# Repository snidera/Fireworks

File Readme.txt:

Fireworks controller.
Make things go boom from your phone...

Free to copy, use at your own risk.  This is somewhat hacked-together as I'm not a professional.    

BeagleboneBlack + i2c connected relay daughter boards 

Uses socket.io bonescript http-auth htpasswd

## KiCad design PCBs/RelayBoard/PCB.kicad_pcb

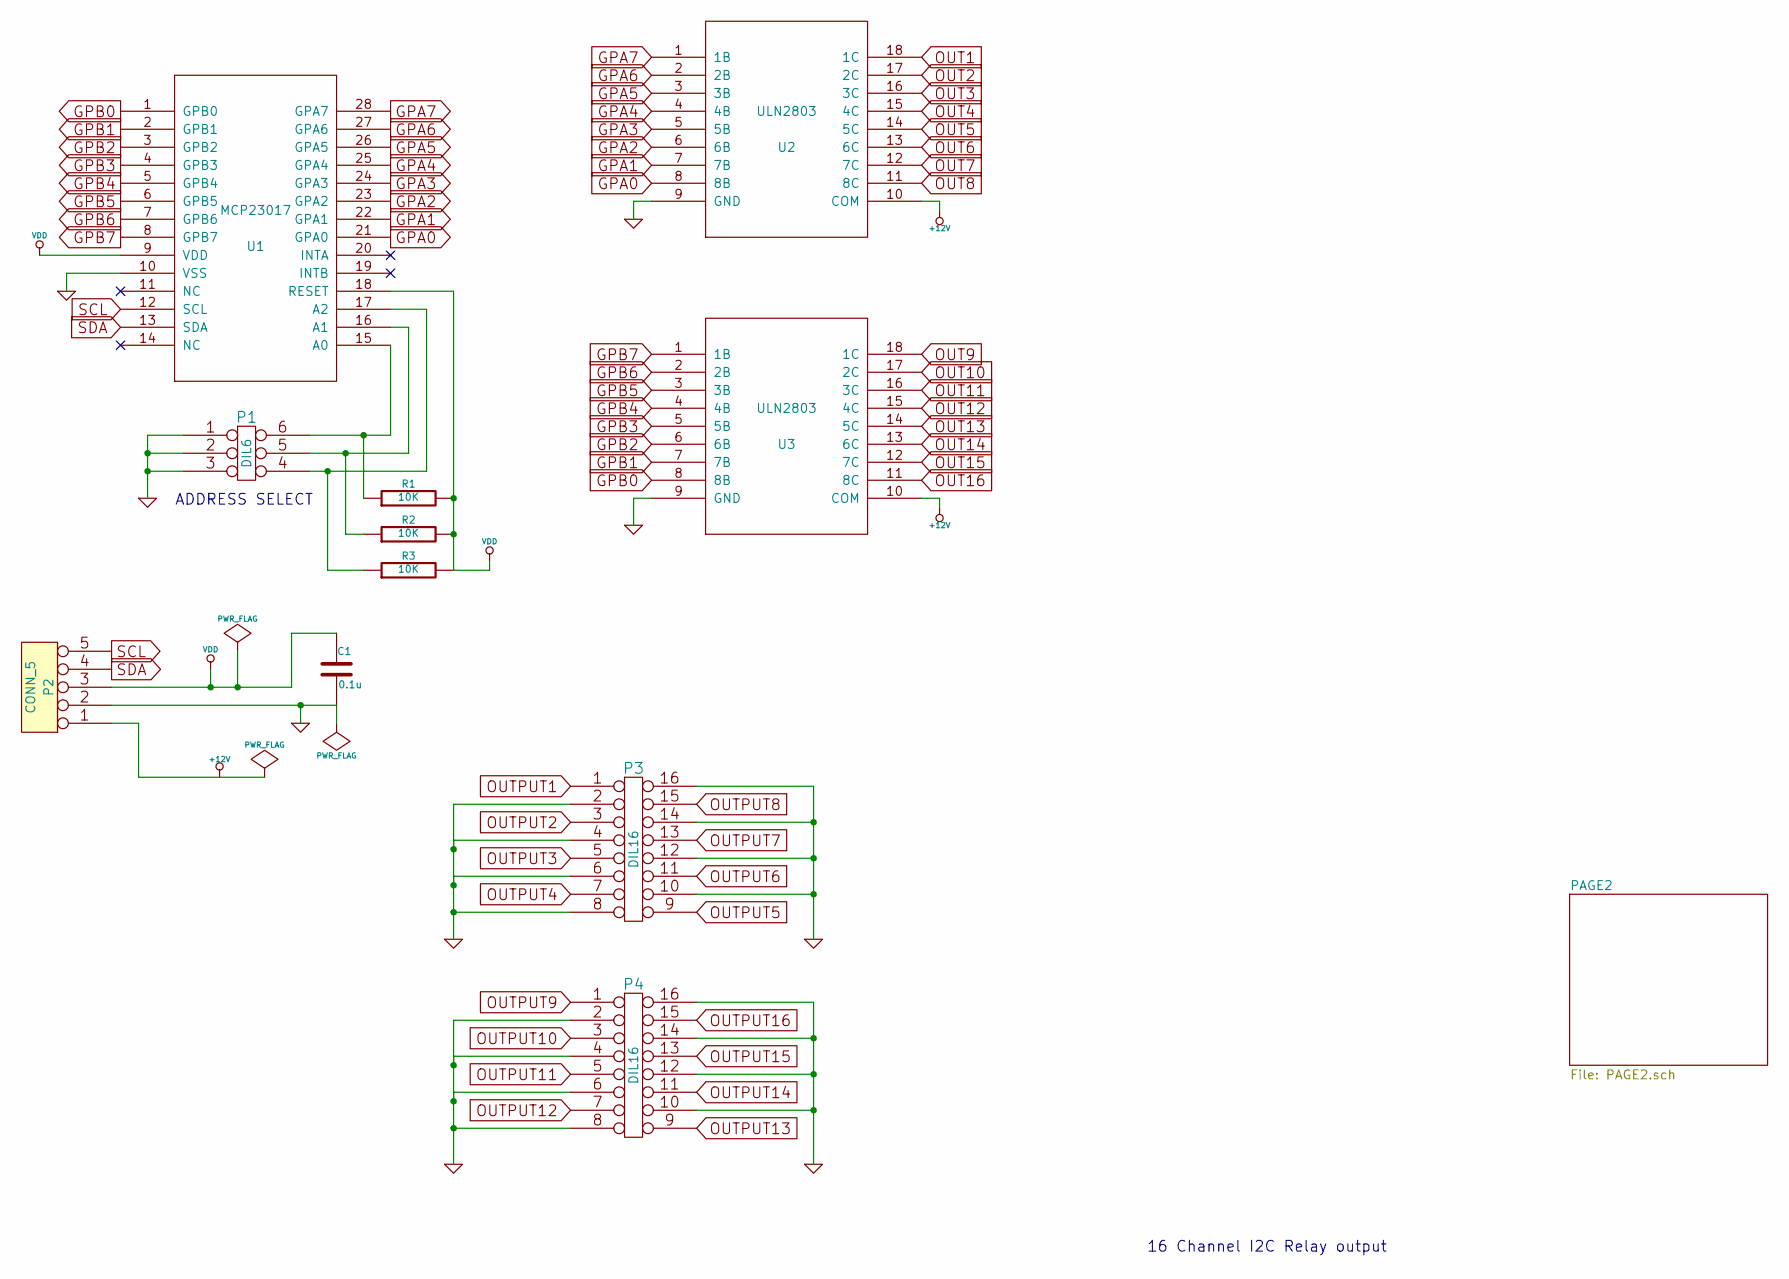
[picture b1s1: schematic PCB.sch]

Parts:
C1: 0.1u
P1: DIL6
P2: CONN_5
P3, P4: DIL16
R1, R2, R3: 10K
U1: MCP23017; MODULE
U2, U3: ULN2803; MODULE

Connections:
GPA0: U1.21 (GPA0), U2.8 (8B)
GPA1: U1.22 (GPA1), U2.7 (7B)
GPA2: U1.23 (GPA2), U2.6 (6B)
GPA3: U1.24 (GPA3), U2.5 (5B)
GPA4: U1.25 (GPA4), U2.4 (4B)
GPA5: U1.26 (GPA5), U2.3 (3B)
GPA6: U1.27 (GPA6), U2.2 (2B)
GPA7: U1.28 (GPA7), U2.1 (1B)
GPB0: U1.1 (GPB0), U3.8 (8B)
GPB1: U1.2 (GPB1), U3.7 (7B)
GPB2: U1.3 (GPB2), U3.6 (6B)
GPB3: U1.4 (GPB3), U3.5 (5B)
GPB4: U1.5 (GPB4), U3.4 (4B)
GPB5: U1.6 (GPB5), U3.3 (3B)
GPB6: U1.7 (GPB6), U3.2 (2B)
GPB7: U1.8 (GPB7), U3.1 (1B)
unnamed: P1.6, R1.1, U1.15 (A0)
unnamed: P1.5, R2.1, U1.16 (A1)
unnamed: P1.4, R3.1, U1.17 (A2)
OUT1: U2.18 (1C); also elsewhere on the board
OUT2: U2.17 (2C); also elsewhere on the board
OUT3: U2.16 (3C); also elsewhere on the board
OUT4: U2.15 (4C); also elsewhere on the board
OUT5: U2.14 (5C); also elsewhere on the board
OUT6: U2.13 (6C); also elsewhere on the board
OUT7: U2.12 (7C); also elsewhere on the board
OUT8: U2.11 (8C); also elsewhere on the board
OUT9: U3.18 (1C); also elsewhere on the board
OUT10: U3.17 (2C); also elsewhere on the board
OUT11: U3.16 (3C); also elsewhere on the board
OUT12: U3.15 (4C); also elsewhere on the board
OUT13: U3.14 (5C); also elsewhere on the board
OUT14: U3.13 (6C); also elsewhere on the board
OUT15: U3.12 (7C); also elsewhere on the board
OUT16: U3.11 (8C); also elsewhere on the board
OUTPUT1: P3.1; also elsewhere on the board
OUTPUT2: P3.3; also elsewhere on the board
OUTPUT3: P3.5; also elsewhere on the board
OUTPUT4: P3.7; also elsewhere on the board
OUTPUT5: P3.9; also elsewhere on the board
OUTPUT6: P3.11; also elsewhere on the board
OUTPUT7: P3.13; also elsewhere on the board
OUTPUT8: P3.15; also elsewhere on the board
OUTPUT9: P4.1; also elsewhere on the board
OUTPUT10: P4.3; also elsewhere on the board
OUTPUT11: P4.5; also elsewhere on the board
OUTPUT12: P4.7; also elsewhere on the board
OUTPUT13: P4.9; also elsewhere on the board
OUTPUT14: P4.11; also elsewhere on the board
OUTPUT15: P4.13; also elsewhere on the board
OUTPUT16: P4.15; also elsewhere on the board
SCL: P2.5, U1.12 (SCL)
SDA: P2.4, U1.13 (SDA)

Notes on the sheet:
16 Channel I2C Relay output
ADDRESS SELECT

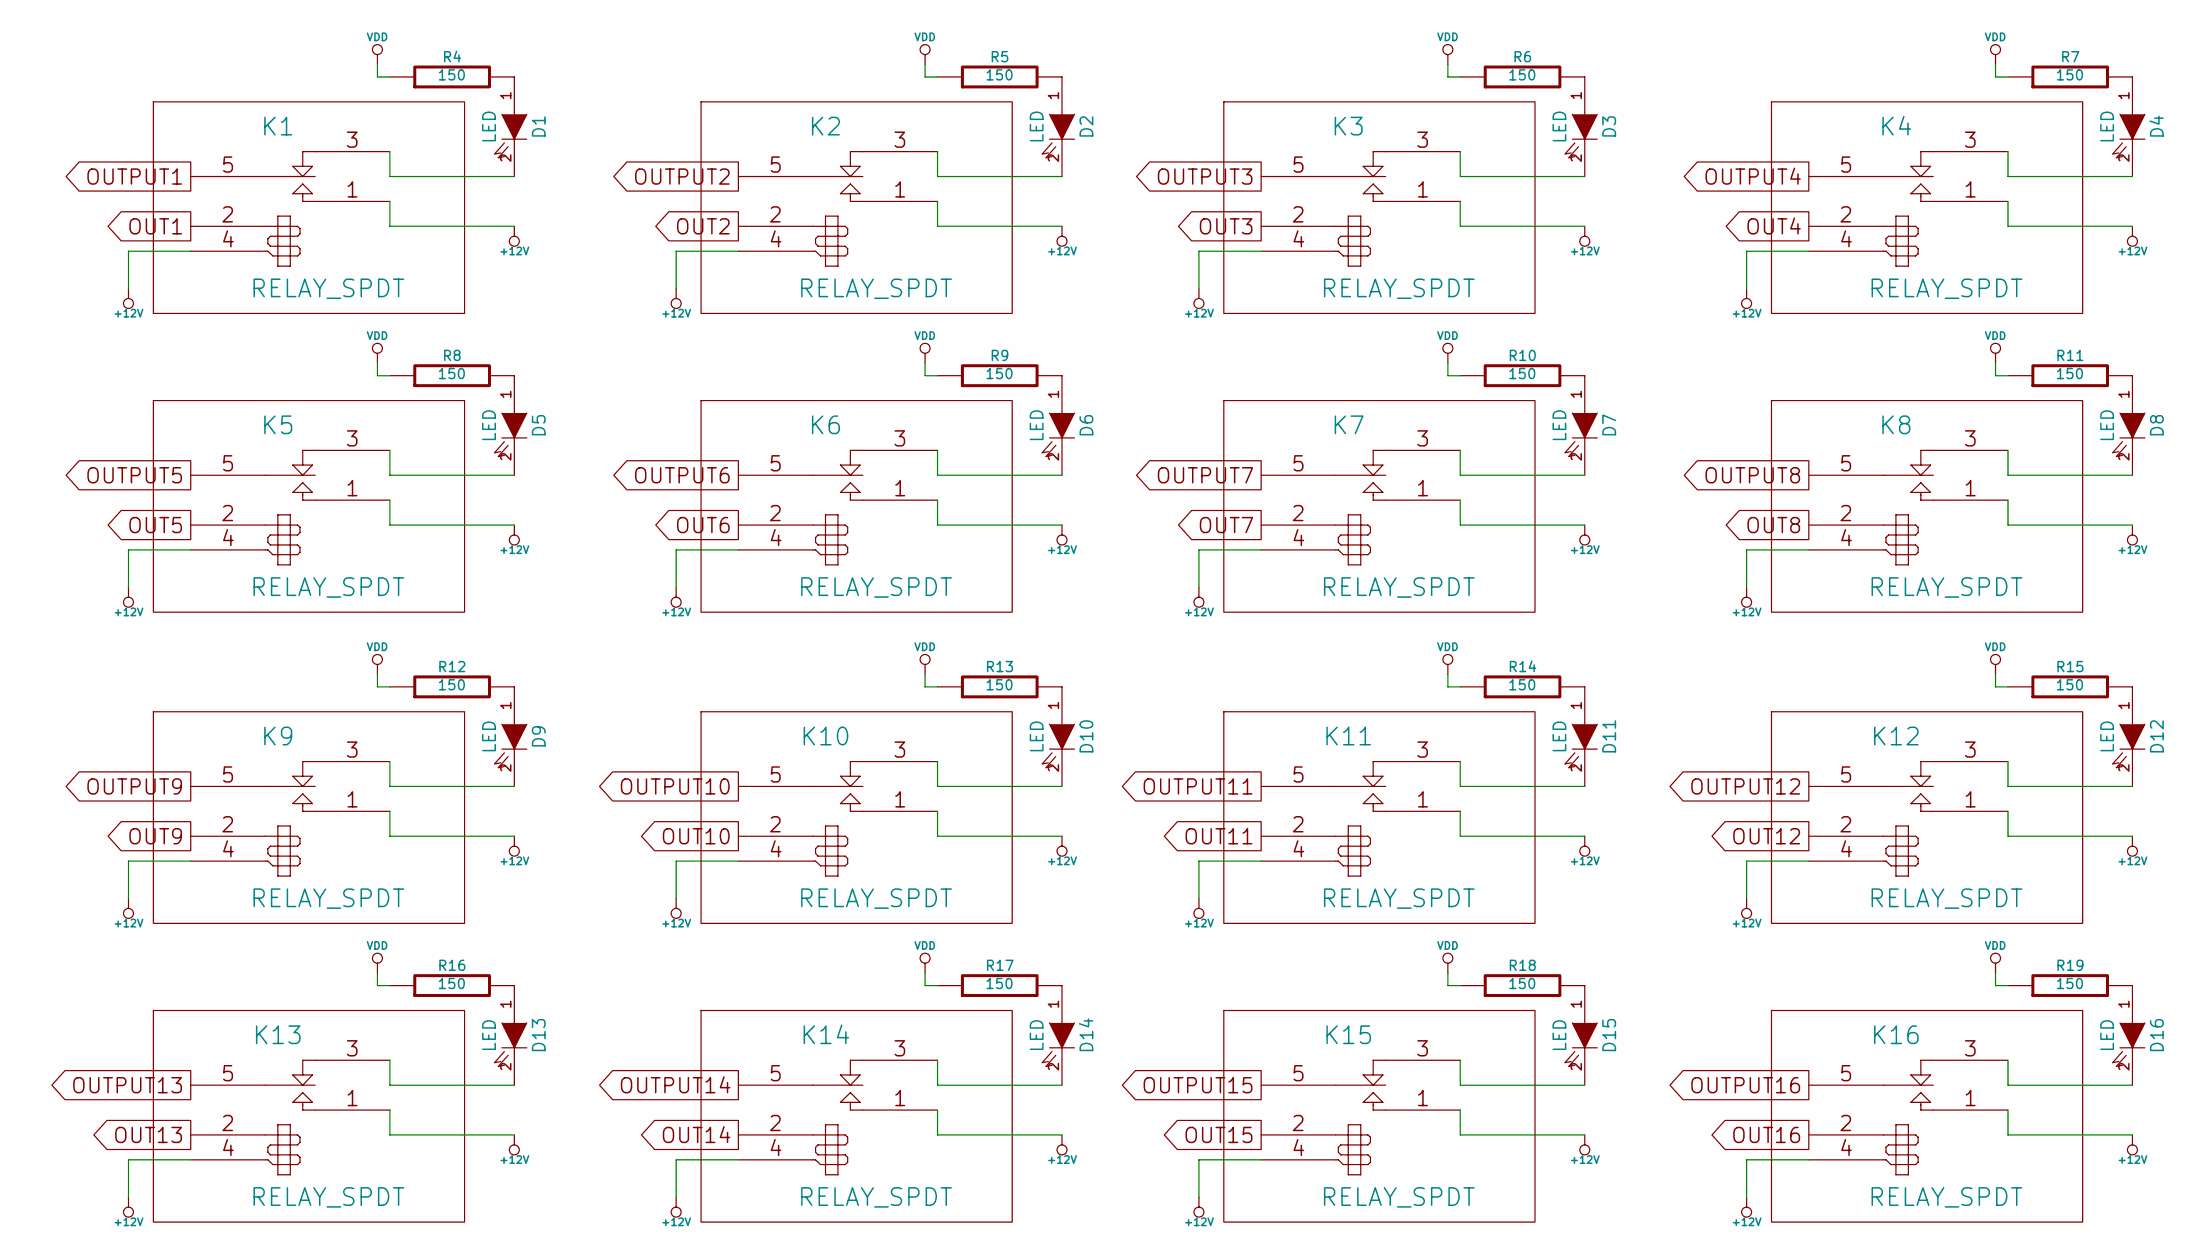
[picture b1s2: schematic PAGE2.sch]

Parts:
D1, D2, D3, D4, D5, D6, D7, D8, D9, D10, D11, D12, D13, D14, D15, D16: LED
K1, K2, K3, K4, K5, K6, K7, K8, K9, K10, K11, K12, K13, K14, K15, K16: RELAY_SPDT
R4, R5, R6, R7, R8, R9, R10, R11, R12, R13, R14, R15, R16, R17, R18, R19: 150

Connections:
unnamed: D11.2 (K), K11.3 (NC)
unnamed: D11.1 (A), R14.2
unnamed: D15.2 (K), K15.3 (NC)
unnamed: D15.1 (A), R18.2
unnamed: D3.2 (K), K3.3 (NC)
unnamed: D3.1 (A), R6.2
unnamed: D7.2 (K), K7.3 (NC)
unnamed: D7.1 (A), R10.2
unnamed: D12.2 (K), K12.3 (NC)
unnamed: D12.1 (A), R15.2
unnamed: D16.2 (K), K16.3 (NC)
unnamed: D16.1 (A), R19.2
unnamed: D4.2 (K), K4.3 (NC)
unnamed: D4.1 (A), R7.2
unnamed: D8.2 (K), K8.3 (NC)
unnamed: D8.1 (A), R11.2
unnamed: D9.2 (K), K9.3 (NC)
unnamed: D9.1 (A), R12.2
unnamed: D13.2 (K), K13.3 (NC)
unnamed: D13.1 (A), R16.2
unnamed: D1.2 (K), K1.3 (NC)
unnamed: D1.1 (A), R4.2
unnamed: D5.2 (K), K5.3 (NC)
unnamed: D5.1 (A), R8.2
unnamed: D10.2 (K), K10.3 (NC)
unnamed: D10.1 (A), R13.2
unnamed: D14.2 (K), K14.3 (NC)
unnamed: D14.1 (A), R17.2
unnamed: D2.2 (K), K2.3 (NC)
unnamed: D2.1 (A), R5.2
unnamed: D6.2 (K), K6.3 (NC)
unnamed: D6.1 (A), R9.2
OUT1: K1.2 (COIL1); also elsewhere on the board
OUT2: K2.2 (COIL1); also elsewhere on the board
OUT3: K3.2 (COIL1); also elsewhere on the board
OUT4: K4.2 (COIL1); also elsewhere on the board
OUT5: K5.2 (COIL1); also elsewhere on the board
OUT6: K6.2 (COIL1); also elsewhere on the board
OUT7: K7.2 (COIL1); also elsewhere on the board
OUT8: K8.2 (COIL1); also elsewhere on the board
OUT9: K9.2 (COIL1); also elsewhere on the board
OUT10: K10.2 (COIL1); also elsewhere on the board
OUT11: K11.2 (COIL1); also elsewhere on the board
OUT12: K12.2 (COIL1); also elsewhere on the board
OUT13: K13.2 (COIL1); also elsewhere on the board
OUT14: K14.2 (COIL1); also elsewhere on the board
OUT15: K15.2 (COIL1); also elsewhere on the board
OUT16: K16.2 (COIL1); also elsewhere on the board
OUTPUT1: K1.5 (COM); also elsewhere on the board
OUTPUT2: K2.5 (COM); also elsewhere on the board
OUTPUT3: K3.5 (COM); also elsewhere on the board
OUTPUT4: K4.5 (COM); also elsewhere on the board
OUTPUT5: K5.5 (COM); also elsewhere on the board
OUTPUT6: K6.5 (COM); also elsewhere on the board
OUTPUT7: K7.5 (COM); also elsewhere on the board
OUTPUT8: K8.5 (COM); also elsewhere on the board
OUTPUT9: K9.5 (COM); also elsewhere on the board
OUTPUT10: K10.5 (COM); also elsewhere on the board
OUTPUT11: K11.5 (COM); also elsewhere on the board
OUTPUT12: K12.5 (COM); also elsewhere on the board
OUTPUT13: K13.5 (COM); also elsewhere on the board
OUTPUT14: K14.5 (COM); also elsewhere on the board
OUTPUT15: K15.5 (COM); also elsewhere on the board
OUTPUT16: K16.5 (COM); also elsewhere on the board

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
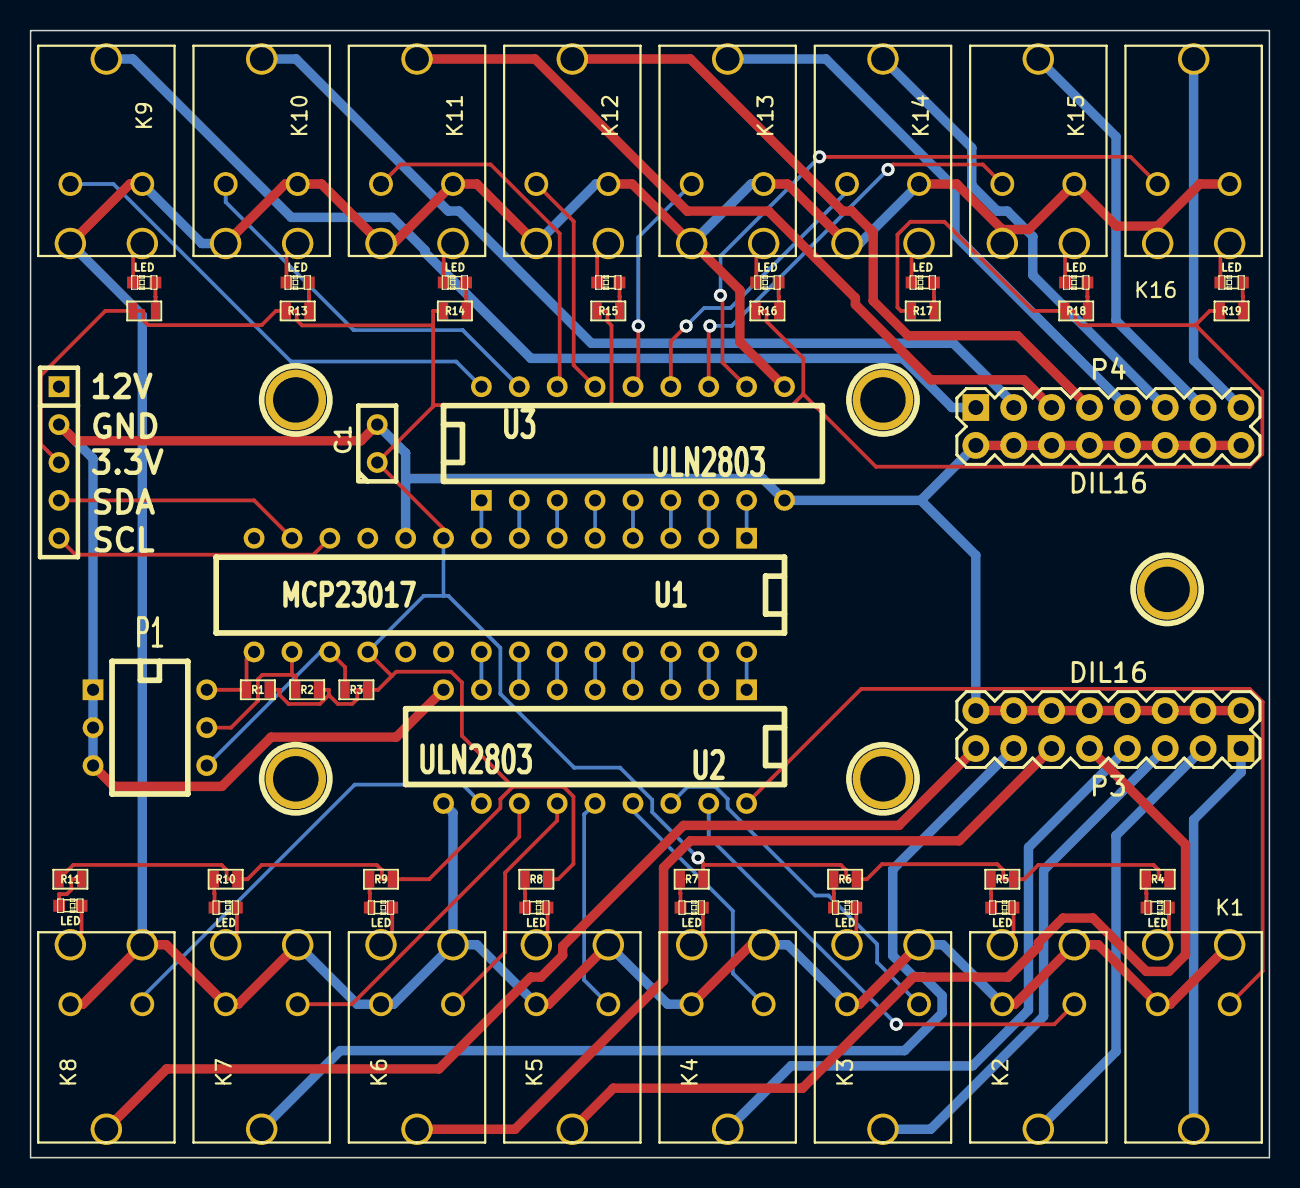
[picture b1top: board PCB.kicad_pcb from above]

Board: 2 copper layers, 83.1 x 75.6 mm, 64 parts (0 on the bottom side), 88 nets.

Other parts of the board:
1PIN1, 1PIN2, 1PIN3, 1PIN4, 1PIN5: P***; 1pin

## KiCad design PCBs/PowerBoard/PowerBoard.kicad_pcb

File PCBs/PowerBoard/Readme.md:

Check the powerboard before using it - I routed C1 on 12V in-line, rather than to gnd.....I'll fix it at some point.

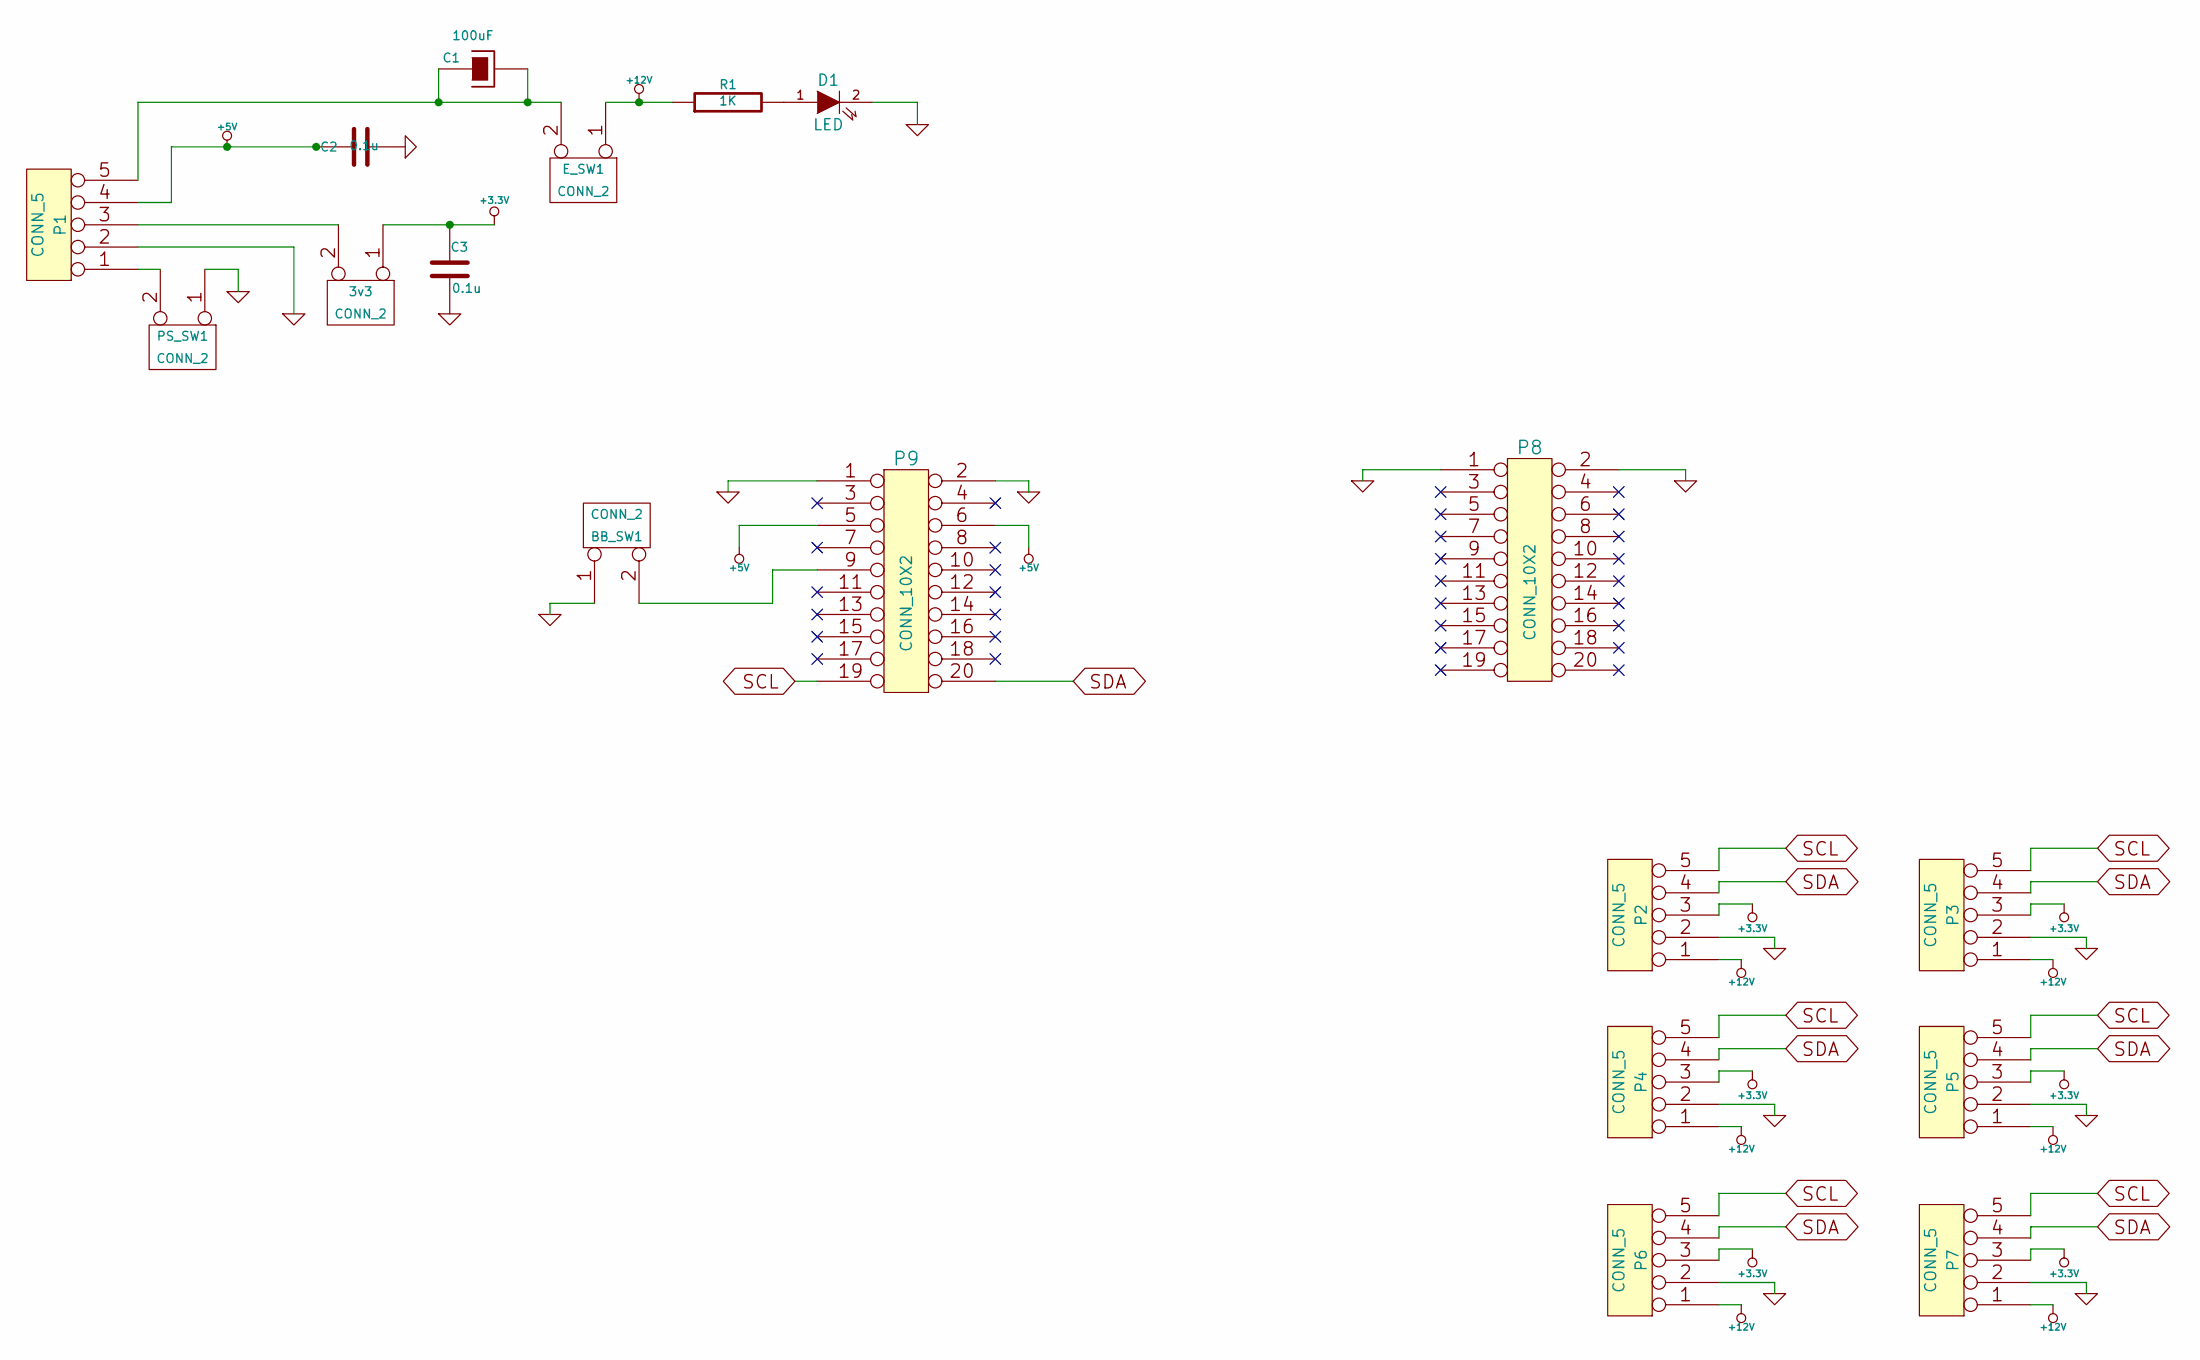
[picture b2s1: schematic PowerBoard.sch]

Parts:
3v3: CONN_2
BB_SW1: CONN_2
C1: 100uF
C2, C3: 0.1u
D1: LED
E_SW1: CONN_2
P1, P2, P3, P4, P5, P6, P7: CONN_5
P8, P9: CONN_10X2
PS_SW1: CONN_2
R1: 1K

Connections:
+3.3V: 3v3.1, C3.1, P2.3, P3.3, P4.3, P5.3, P6.3, P7.3
+5V: C2.1, P1.4, P9.5, P9.6
+12V: E_SW1.1, P2.1, P3.1, P4.1, P5.1, P6.1, P7.1, R1.1
GND: BB_SW1.1, C2.2, C3.2, D1.2 (K), P1.2, P2.2, P3.2, P4.2, P5.2, P6.2, P7.2, P8.1, P8.2, P9.1, P9.2, PS_SW1.1
unnamed: BB_SW1.2 (PM), P9.9
unnamed: 3v3.2 (PM), P1.3
unnamed: P1.1, PS_SW1.2 (PM)
unnamed: D1.1 (A), R1.2
unnamed: C1.1, C1.2, E_SW1.2 (PM), P1.5
SCL: P2.5, P3.5, P4.5, P5.5, P6.5, P7.5, P9.19
SDA: P2.4, P3.4, P4.4, P5.4, P6.4, P7.4, P9.20

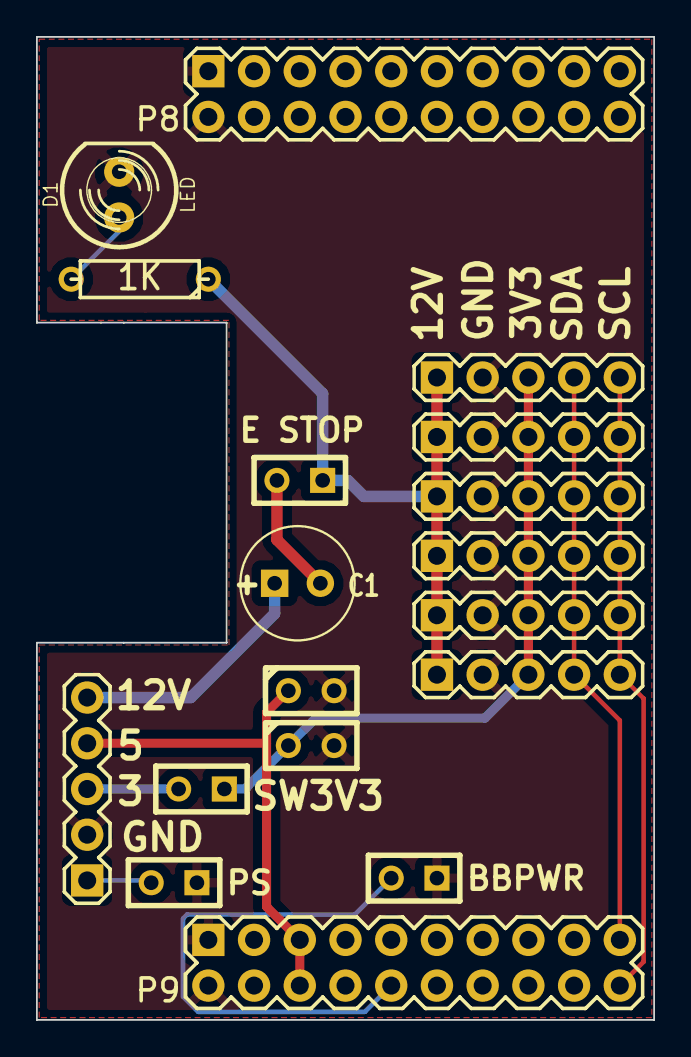
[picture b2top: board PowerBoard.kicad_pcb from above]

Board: 2 copper layers, 34.3 x 54.6 mm, 18 parts (0 on the bottom side), 11 nets.

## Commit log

2014-07-15 Add Readme
2014-07-15 Added BasicAuth & index.html
2014-07-15 add passwd file
2014-07-15 fix BasicAuth
2014-07-15 add KiCAD PCB files
2014-07-21 set time to 750ms
